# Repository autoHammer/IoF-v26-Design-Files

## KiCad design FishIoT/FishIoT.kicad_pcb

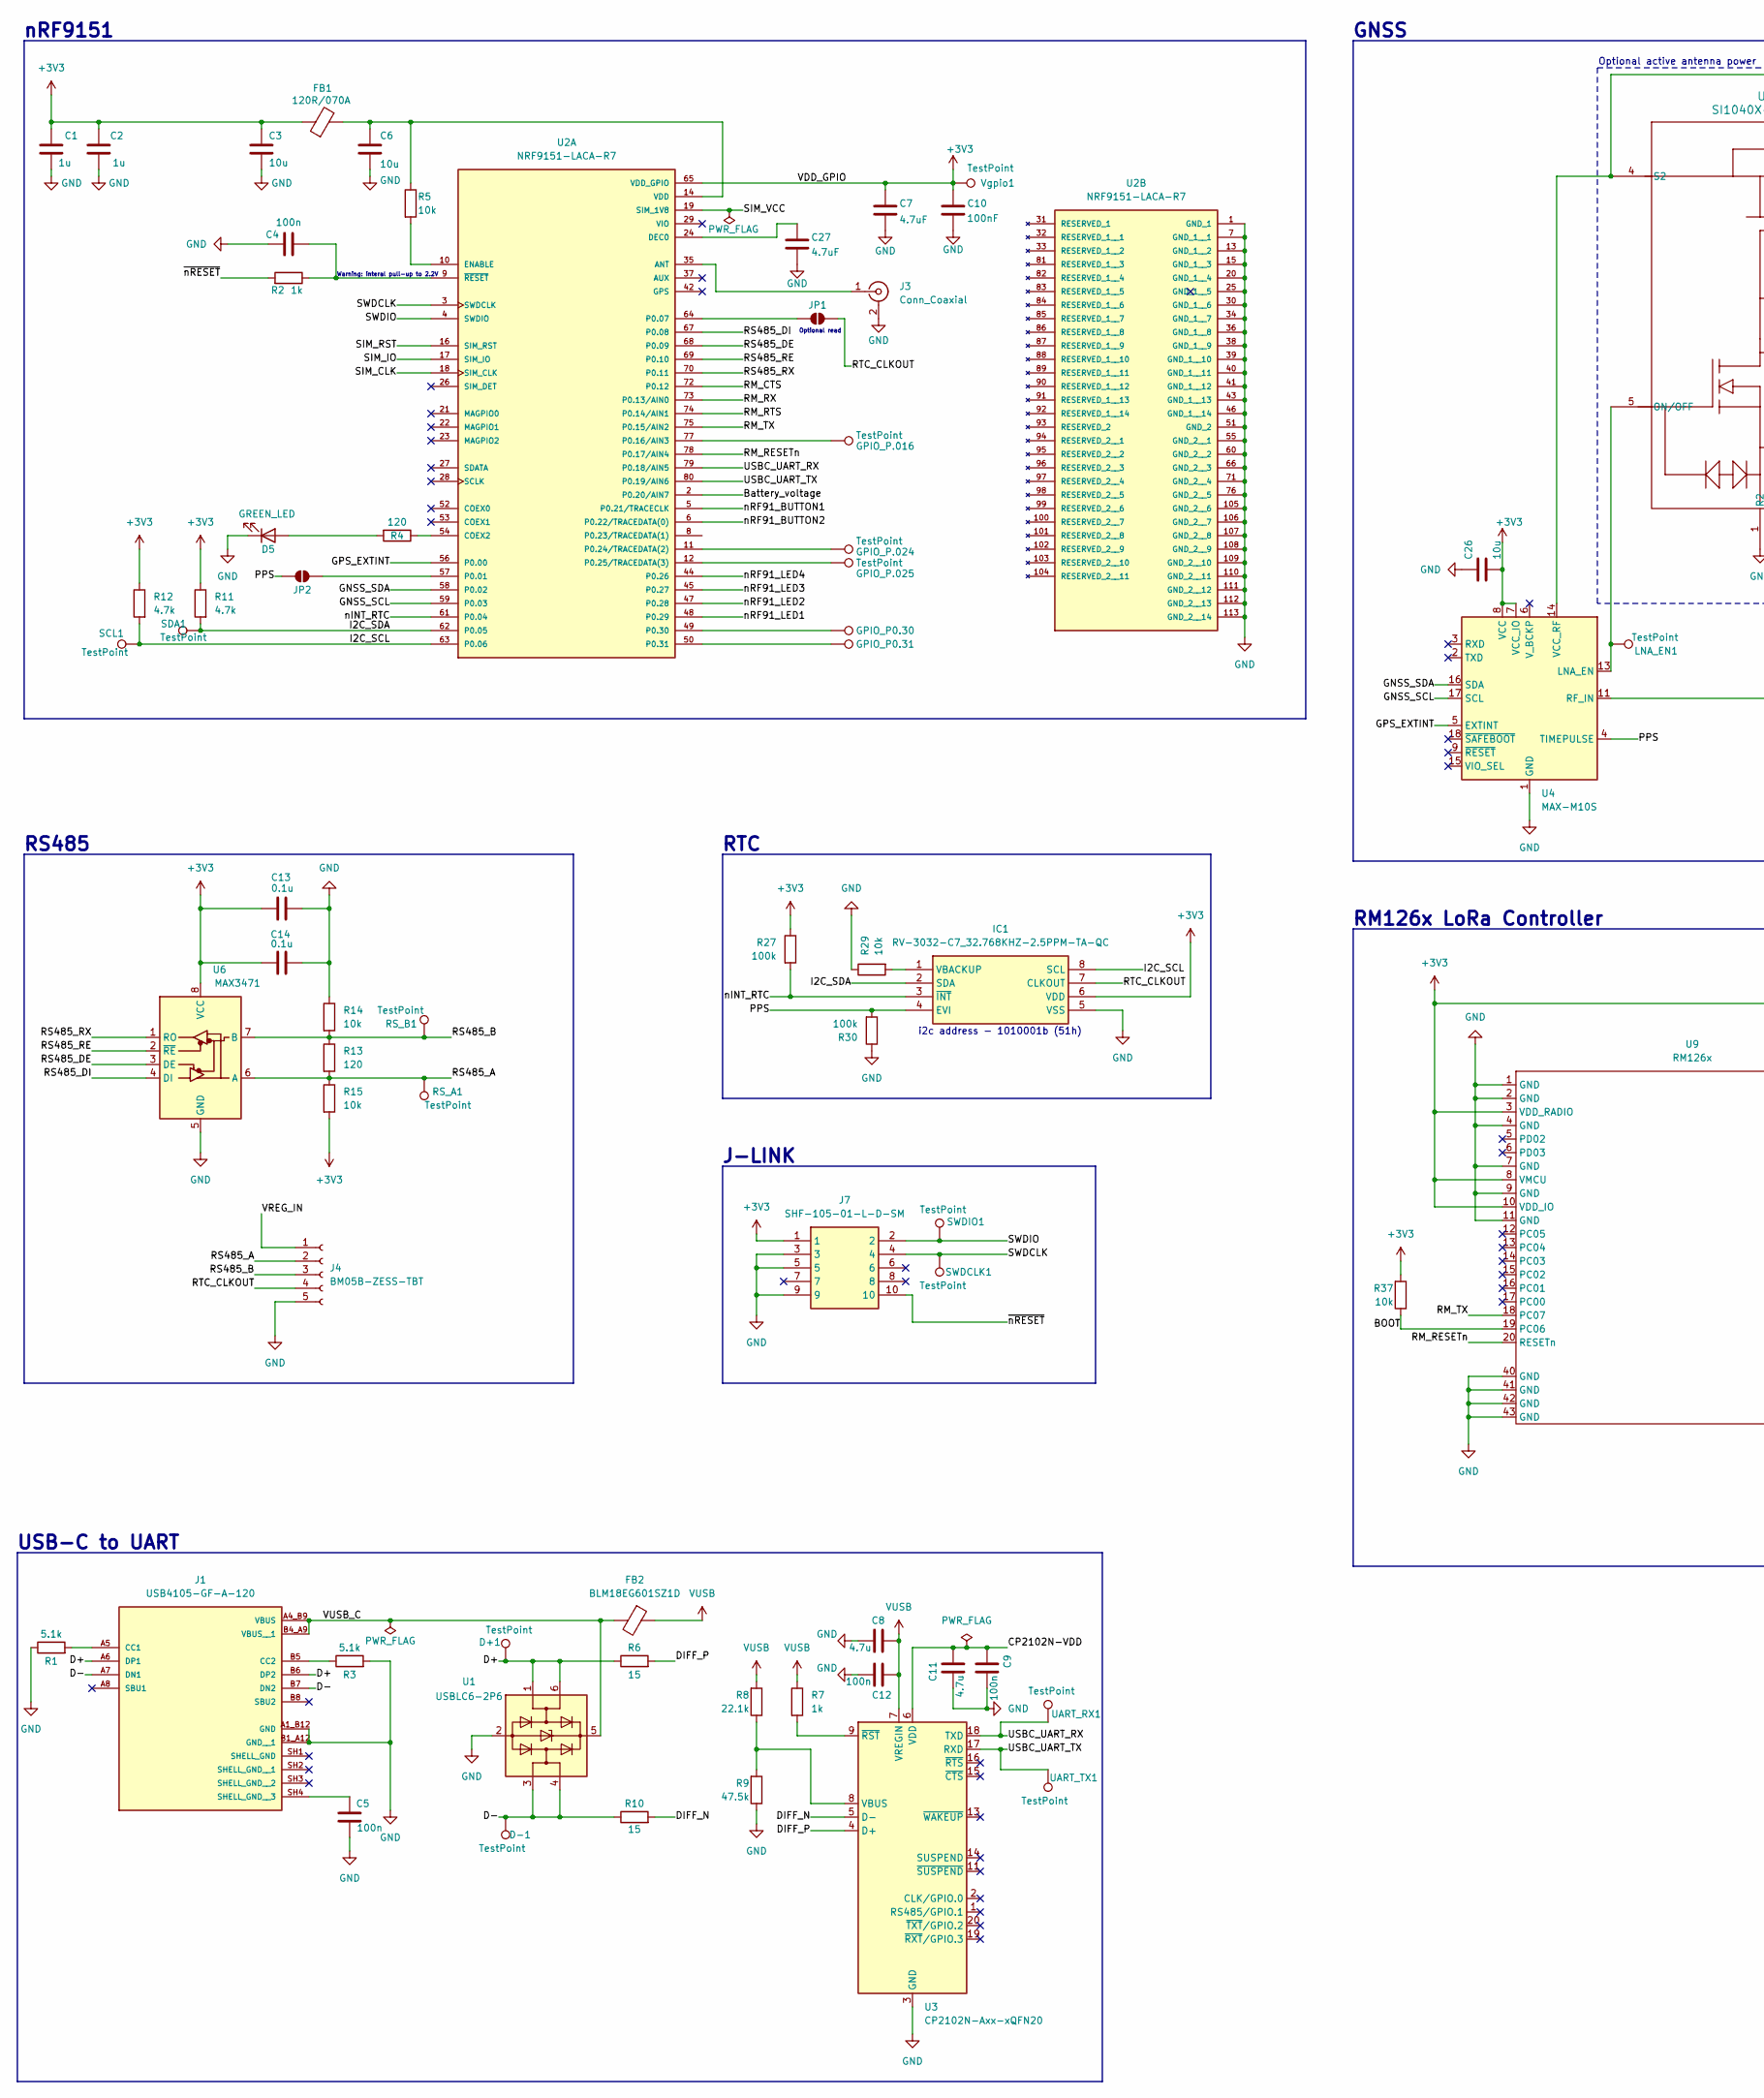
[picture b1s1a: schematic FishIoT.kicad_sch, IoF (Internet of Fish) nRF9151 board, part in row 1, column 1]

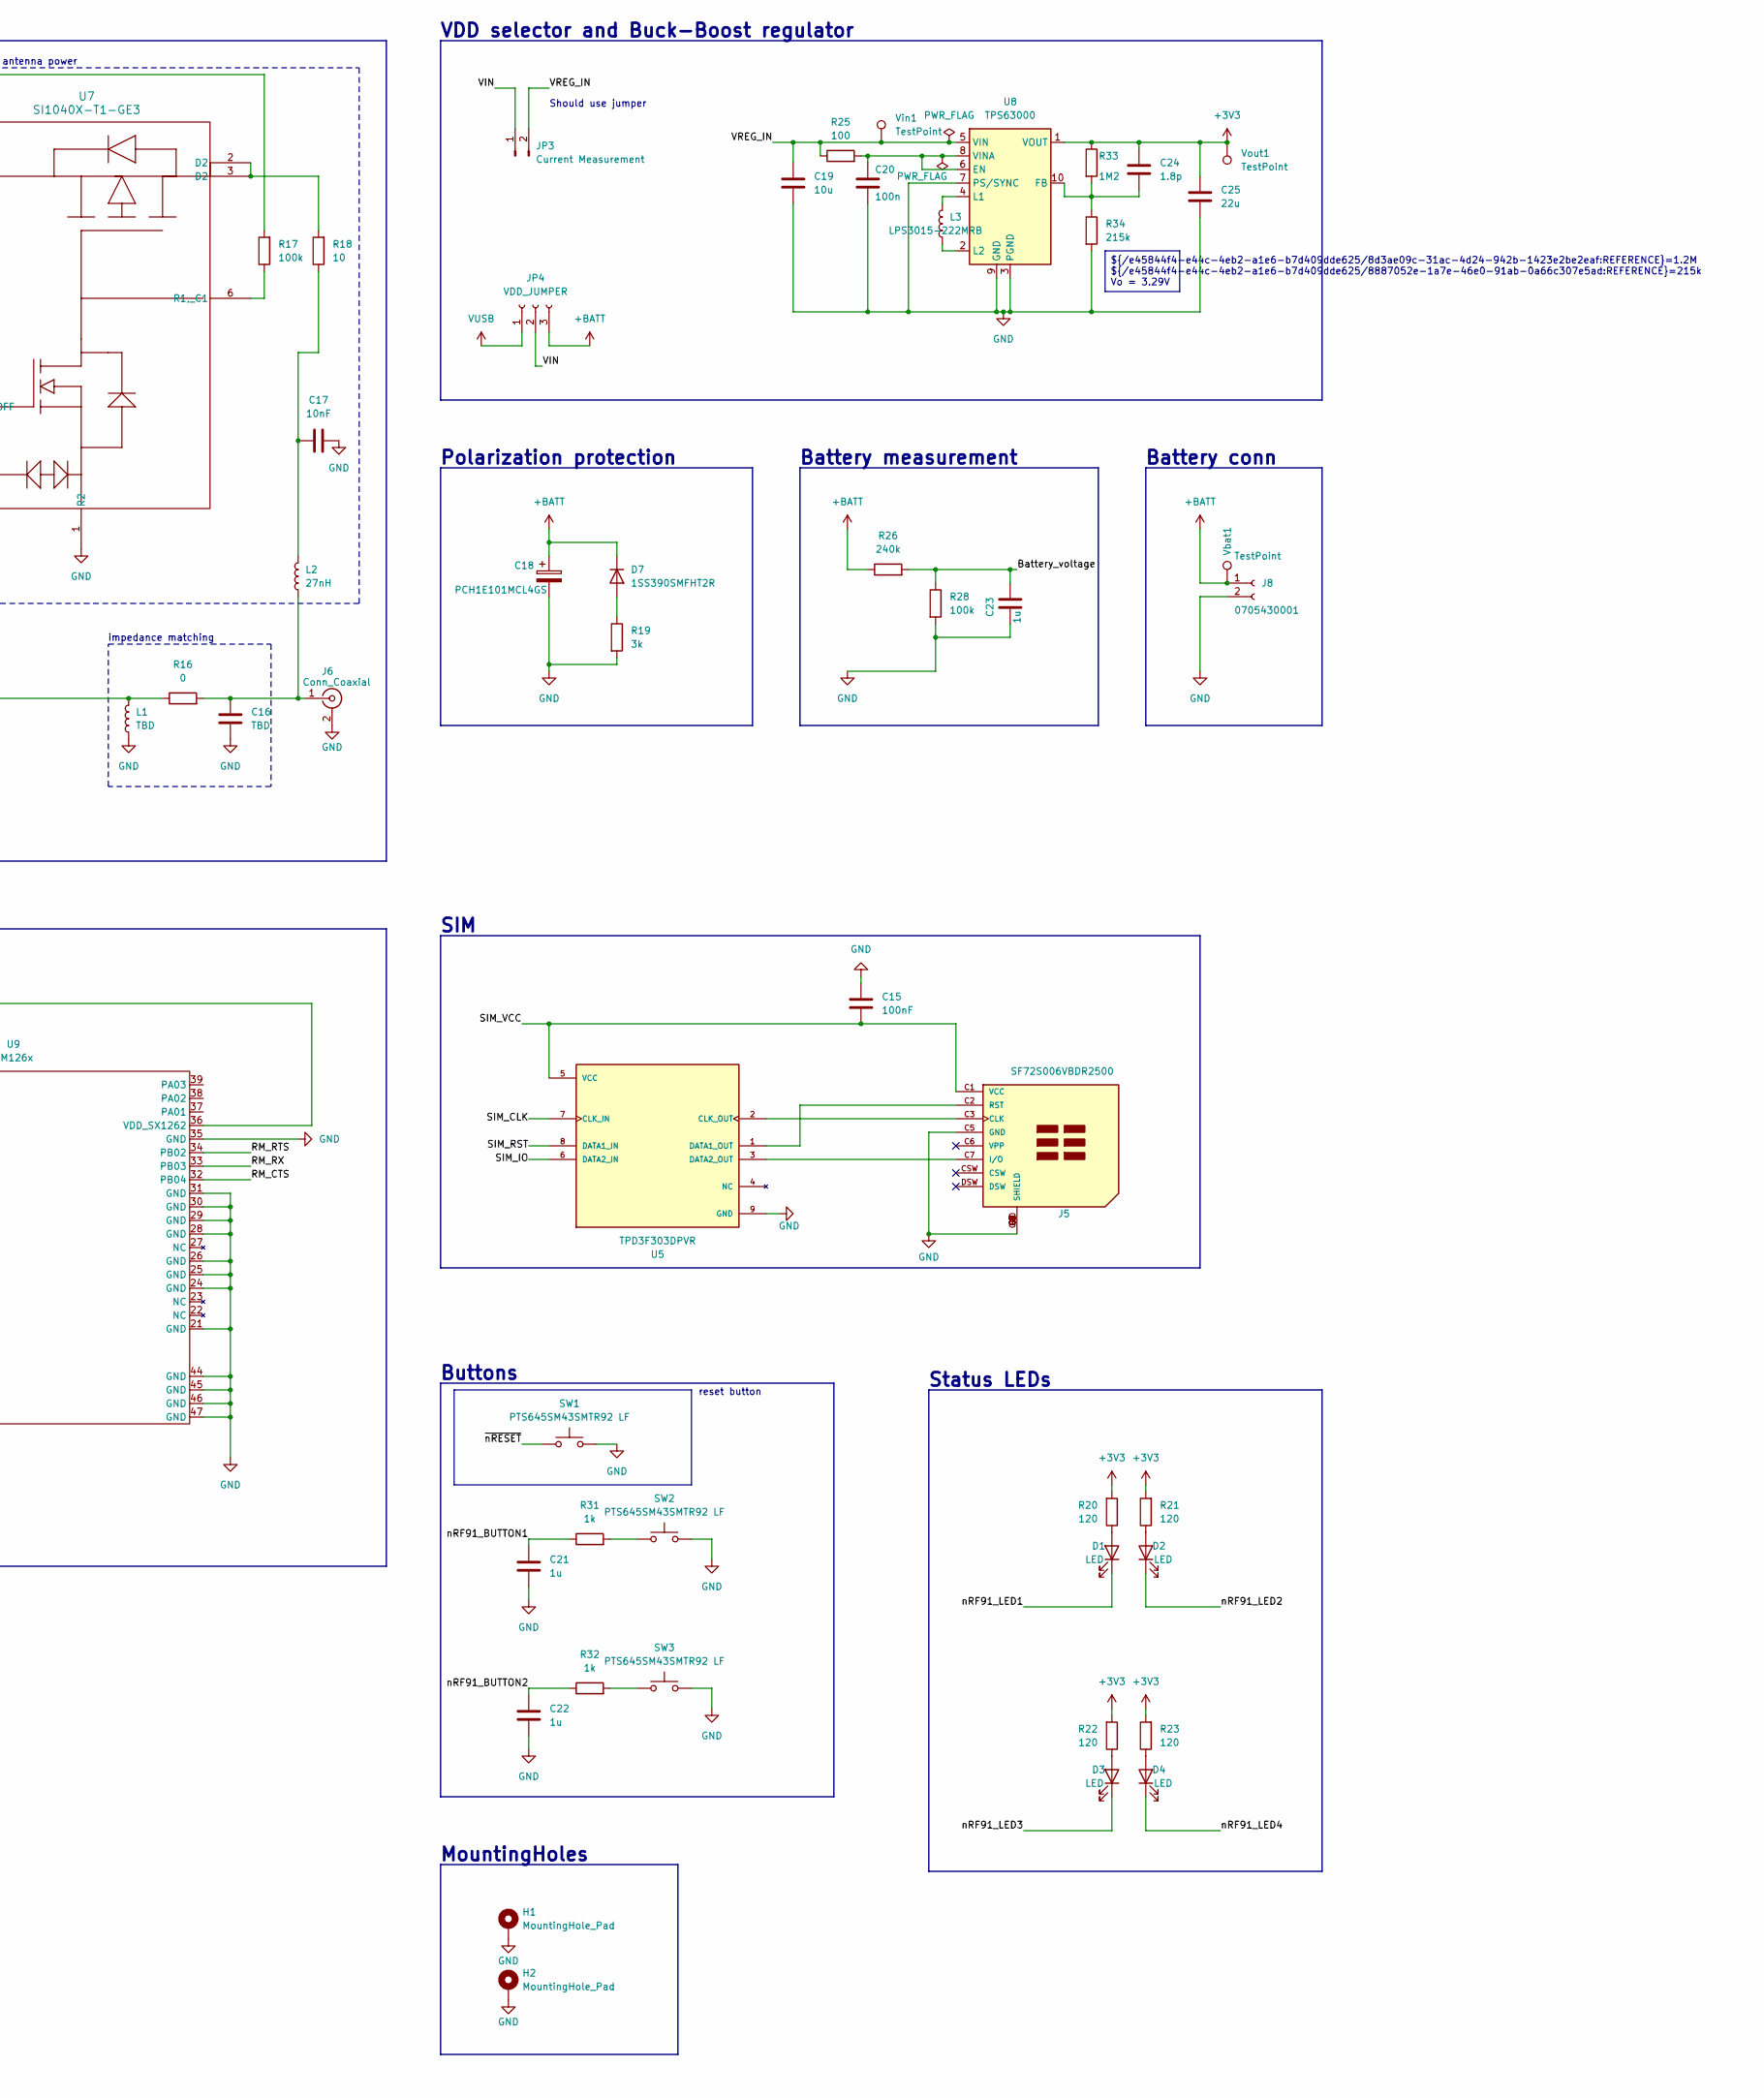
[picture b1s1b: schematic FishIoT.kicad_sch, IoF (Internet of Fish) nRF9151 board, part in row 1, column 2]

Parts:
C1, C2, C21, C22, C23: 1u; C_0603_1608Metric
C3, C6, C19, C26: 10u; C_0603_1608Metric
C4, C5, C9, C12, C20: 100n; C_0603_1608Metric
C7, C27: 4.7uF; C_0603_1608Metric
C8, C11: 4.7u; C_0603_1608Metric
C10, C15: 100nF; C_0603_1608Metric
C13, C14: 0.1u; C_0603_1608Metric
C16: TBD; C_0603_1608Metric
C17: 10nF; C_0603_1608Metric
C18: PCH1E101MCL4GS; CP_Elec_6.3x7.7
C24: 1.8p; C_0603_1608Metric
C25: 22u; C_0603_1608Metric
D1, D2, D3, D4: LED; LED_0603_1608Metric
D5: GREEN_LED; LED_0603_1608Metric
D7: 1SS390SMFHT2R; D_SOD-523
D+1: TestPoint; TestPoint_Pad_D1.0mm
D-1: TestPoint; TestPoint_Pad_D1.0mm
FB1: 120R/070A; L_0603_1608Metric
FB2: BLM18EG601SZ1D; L_0603_1608Metric
GPIO_P0.30, GPIO_P0.31, GPIO_P.016, GPIO_P.024, GPIO_P.025: TestPoint; TestPoint_Pad_D1.0mm
H1, H2: MountingHole_Pad; MountingHole_3mm_Pad_Via
IC1: RV-3032-C7_32.768KHZ-2.5PPM-TA-QC; RV3032C7; Mouser Part Number 428-203803-MG01
J1: USB4105-GF-A-120; GCT_USB4105-GF-A-120; PARTREV B3
J3, J6: Conn_Coaxial; LINX_CONUFL001-SMD-T
J4: BM05B-ZESS-TBT; BM05BZESSTBTLFSN
J5: SF72S006VBDR2500; JAE_SF72S006VBDR2500
J7: SHF-105-01-L-D-SM; SHF-105-01-X-D-SM; Mouser Part Number 200-SHF10501LDSM
J8: 0705430001; MOLEX_0705430001
JP1, JP2: SolderJumper_2_Open; SolderJumper-2_P1.3mm_Open_RoundedPad1.0x1.5mm
JP3: Current Measurement; PinHeader_1x02_P2.54mm_Vertical
JP4: VDD_JUMPER; PinHeader_1x03_P2.54mm_Vertical
L1: TBD; L_0603_1608Metric
L2: 27nH; L_0603_1608Metric
L3: LPS3015-222MRB; L_Vishay_IHLP-1212
LNA_EN1: TestPoint; TestPoint_Pad_D1.0mm
R1, R3: 5.1k; R_0603_1608Metric
R2, R7, R31, R32: 1k; R_0603_1608Metric
R4, R13, R20, R21, R22, R23: 120; R_0603_1608Metric
R5, R14, R15, R29, R37: 10k; R_0603_1608Metric
R6, R10: 15; R_0603_1608Metric
R8: 22.1k; R_0603_1608Metric
R9: 47.5k; R_0603_1608Metric
R11, R12: 4.7k; R_0603_1608Metric
R16: 0; R_0603_1608Metric
R17, R27, R28, R30: 100k; R_0603_1608Metric
R18: 10; R_0603_1608Metric
R19: 3k; R_0603_1608Metric
R25: 100; R_0603_1608Metric
R26: 240k; R_0603_1608Metric
R33: 1M2; R_0603_1608Metric
R34: 215k; R_0603_1608Metric
RS_A1: TestPoint; TestPoint_Pad_D1.0mm
RS_B1: TestPoint; TestPoint_Pad_D1.0mm
SCL1: TestPoint; TestPoint_Pad_D1.0mm
SDA1: TestPoint; TestPoint_Pad_D1.0mm
SW1, SW2, SW3: PTS645SM43SMTR92 LF; SW_Push_1P1T_NO_6x6mm_H9.5mm
SWDCLK1: TestPoint; TestPoint_Pad_D1.0mm
SWDIO1: TestPoint; TestPoint_Pad_D1.0mm
U1: USBLC6-2P6; SOT-666
U2: NRF9151-LACA-R7; XCVR_NRF9151-LACA-R7; PARTREV 2025-10-21
U3: CP2102N-Axx-xQFN20; SiliconLabs_QFN-20-1EP_3x3mm_P0.5mm_EP1.8x1.8mm
U4: MAX-M10S; ublox_MAX
U5: TPD3F303DPVR; SON50P210X160X65-9N
U6: MAX3471; TSSOP-8_3x3mm_P0.65mm
U7: SI1040X-T1-GE3; SON_0X-T1-GE3_VIS
U8: TPS63000; Texas_DRC0010J_ThermalVias
U9: RM126x; Laird, RM126X
UART_RX1: TestPoint; TestPoint_Pad_D1.0mm
UART_TX1: TestPoint; TestPoint_Pad_D1.0mm
Vbat1: TestPoint; TestPoint_Pad_D1.0mm
Vgpio1: TestPoint; TestPoint_Pad_D1.0mm
Vin1: TestPoint; TestPoint_Pad_D1.0mm
Vout1: TestPoint; TestPoint_Pad_D1.0mm

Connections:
+3V3: C1.2, C2.2, C3.2, C7.1, C10.1, C13.1, C14.2, C24.1, C25.1, C26.2, FB1.1, IC1.6 (VDD), J7.1, R11.1, R12.1, R15.2, R20.2, R21.2, R22.2, R23.2, R27.1, R33.1, R37.2, U2.65 (VDD_GPIO), U4.7 (VCC_IO), U4.8 (VCC), U6.8 (VCC), U8.1 (VOUT), U9.3 (VDD_RADIO), U9.8 (VMCU), U9.10 (VDD_IO), U9.36 (VDD_SX1262), Vgpio1.1, Vout1.1
+BATT: C18.1, D7.1 (K), J8.1, JP4.3, R26.1, Vbat1.1
/BOOT: R37.1, U9.19 (PC06)
/Battery_voltage: C23.2, R26.2, R28.1, U2.2 (P0.20/AIN7)
/CP2102N-VDD: C9.2, C11.2, U3.6 (VDD)
/D+: D+1.1, J1.A6 (DP1), J1.B6 (DP2), R6.1, U1.1 (I/O1), U1.6 (I/O1)
/D-: D-1.1, J1.A7 (DN1), J1.B7 (DN2), R10.1, U1.3 (I/O2), U1.4 (I/O2)
/DIFF_N: R10.2, U3.5 (D-)
/DIFF_P: R6.2, U3.4 (D+)
/GNSS_SCL: U2.59 (P0.03), U4.17 (SCL)
/GNSS_SDA: U2.58 (P0.02), U4.16 (SDA)
/GPS_EXTINT: U2.56 (P0.00), U4.5 (EXTINT)
/I2C_SCL: IC1.8 (SCL), R12.2, SCL1.1, U2.63 (P0.06)
/I2C_SDA: IC1.2 (SDA), R11.2, SDA1.1, U2.62 (P0.05)
/PPS: IC1.4 (EVI), JP2.2 (B), R30.2, U4.4 (TIMEPULSE)
/RM_CTS: U2.72 (P0.12), U9.32 (PB04)
/RM_RESETn: U2.78 (P0.17/AIN4), U9.20 (RESETn)
/RM_RTS: U2.74 (P0.14/AIN1), U9.34 (PB02)
/RM_RX: U2.73 (P0.13/AIN0), U9.33 (PB03)
/RM_TX: U2.75 (P0.15/AIN2), U9.18 (PC07)
/RS485_A: J4.2, R13.2, R15.1, RS_A1.1, U6.6 (A)
/RS485_B: J4.3, R13.1, R14.2, RS_B1.1, U6.7 (B)
/RS485_DE: U2.68 (P0.09), U6.3 (DE)
/RS485_DI: U2.67 (P0.08), U6.4 (DI)
/RS485_RE: U2.69 (P0.10), U6.2 (~RE)
/RS485_RX: U2.70 (P0.11), U6.1 (RO)
/RTC_CLKOUT: IC1.7 (CLKOUT), J4.4, JP1.2 (B)
/SIM_CLK: U2.18 (SIM_CLK), U5.7 (CLK_IN)
/SIM_IO: U2.17 (SIM_IO), U5.6 (DATA2_IN)
/SIM_RST: U2.16 (SIM_RST), U5.8 (DATA1_IN)
/SIM_VCC: C15.2, J5.C1 (VCC), U2.19 (SIM_1V8), U5.5 (VCC)
/SWDCLK: J7.4, SWDCLK1.1, U2.3 (SWDCLK)
/SWDIO: J7.2, SWDIO1.1, U2.4 (SWDIO)
/USBC_UART_RX: U2.79 (P0.18/AIN5), U3.18 (TXD), UART_RX1.1
/USBC_UART_TX: U2.80 (P0.19/AIN6), U3.17 (RXD), UART_TX1.1
/VIN: JP3.1, JP4.2
/VREG_IN: C19.1, J4.1, JP3.2, R25.1, U8.5 (VIN), Vin1.1
/VUSB_C: FB2.2, J1.A4_B9 (VBUS), J1.B4_A9 (VBUS__1), U1.5 (VBUS)
/nINT_RTC: IC1.3 (~INT), R27.2, U2.61 (P0.04)
/nRF91_BUTTON1: C21.1, R31.1, U2.5 (P0.21/TRACECLK)
/nRF91_BUTTON2: C22.1, R32.1, U2.6 (P0.22/TRACEDATA(0))
/nRF91_LED1: D1.1 (K), U2.48 (P0.29)
/nRF91_LED2: D2.1 (K), U2.47 (P0.28)
/nRF91_LED3: D3.1 (K), U2.45 (P0.27)
/nRF91_LED4: D4.1 (K), U2.44 (P0.26)
/~nRESET: J7.10, R2.2, SW1.1
GND: C1.1, C2.1, C3.1, C4.1, C5.1, C6.2, C7.2, C8.1, C9.1, C10.2, C11.1, C12.1, C13.2, C14.1, C15.1, C16.2, C17.2, C18.2, C19.2, C20.2, C21.2, C22.2, C23.1, C25.2, C26.1, C27.2, D5.1 (K), H1.1, H2.1, IC1.5 (VSS), J1.A1_B12 (GND), J1.B1_A12 (GND__1), J3.2 (Ext), J4.5, J5.C5 (GND), J5.G1 (SHIELD), J5.G2 (SHIELD), J5.G3 (SHIELD), J5.G4 (SHIELD), J5.G5 (SHIELD), J5.G6 (SHIELD), J5.G7 (SHIELD), J5.G8 (SHIELD), J5.G9 (SHIELD), J5.G10 (SHIELD), J6.2 (Ext), J7.3, J7.5, J7.9, J8.2, L1.1, R1.1, R3.2, R9.1, R14.1, R19.2, R28.2, R29.1, R30.1, R34.2, SW1.2, SW2.2, SW3.2, U1.2 (GND), U2.1 (GND_1), U2.7 (GND_1__1), U2.13 (GND_1__2), U2.15 (GND_1__3), U2.20 (GND_1__4), U2.25 (GND_1__5), U2.30 (GND_1__6), U2.34 (GND_1__7), U2.36 (GND_1__8), U2.38 (GND_1__9), U2.39 (GND_1__10), U2.40 (GND_1__11), U2.41 (GND_1__12), U2.43 (GND_1__13), U2.46 (GND_1__14), U2.51 (GND_2), U2.55 (GND_2__1), U2.60 (GND_2__2), U2.66 (GND_2__3), U2.71 (GND_2__4), U2.76 (GND_2__5), U2.105 (GND_2__6), U2.106 (GND_2__7), U2.107 (GND_2__8), U2.108 (GND_2__9), U2.109 (GND_2__10), U2.110 (GND_2__11), U2.111 (GND_2__12), U2.112 (GND_2__13), U2.113 (GND_2__14), U3.3 (GND), U3.12 (GND), U3.21 (GND), U4.1 (GND), U4.10 (GND), U4.12 (GND), U5.9 (GND), U6.5 (GND), U7.1 (R2), U8.3 (PGND), U8.7 (PS/SYNC), U8.9 (GND), U8.11 (PGND), U9.1 (GND), U9.2 (GND), U9.4 (GND), U9.7 (GND), U9.9 (GND), U9.11 (GND), U9.21 (GND), U9.24 (GND), U9.25 (GND), U9.26 (GND), U9.28 (GND), U9.29 (GND), U9.30 (GND), U9.31 (GND), U9.35 (GND), U9.40 (GND), U9.41 (GND), U9.42 (GND), U9.43 (GND), U9.44 (GND), U9.45 (GND), U9.46 (GND), U9.47 (GND)
unnamed: C17.1, L2.2, R18.1
unnamed: D1.2 (A), R20.1
unnamed: D2.2 (A), R21.1
unnamed: D3.2 (A), R22.1
unnamed: D4.2 (A), R23.1
unnamed: D5.2 (A), R4.2
unnamed: D7.2 (A), R19.1
unnamed: IC1.1 (VBACKUP), R29.2
unnamed: J1.A5 (CC1), R1.2
unnamed: J1.B5 (CC2), R3.1
unnamed: C5.2, J1.SH4 (SHELL_GND__3)
unnamed: J3.1 (In), U2.35 (ANT)
unnamed: J5.C3 (CLK), U5.2 (CLK_OUT)
unnamed: J5.C7 (I/O), U5.3 (DATA2_OUT)
unnamed: J5.C2 (RST), U5.1 (DATA1_OUT)
unnamed: C16.1, J6.1 (In), L2.1, R16.2
unnamed: JP1.1 (A), U2.64 (P0.07)
unnamed: JP2.1 (A), U2.57 (P0.01)
unnamed: R18.2, U7.2 (D2), U7.3 (D2)
unnamed: R31.2, SW2.1
unnamed: R32.2, SW3.1
unnamed: R4.1, U2.54 (COEX2)
unnamed: C27.1, U2.24 (DEC0)
unnamed: R5.2, U2.10 (ENABLE)
unnamed: GPIO_P.016.1, U2.77 (P0.16/AIN3)
unnamed: GPIO_P.024.1, U2.11 (P0.24/TRACEDATA(2))
unnamed: GPIO_P.025.1, U2.12 (P0.25/TRACEDATA(3))
unnamed: GPIO_P0.30.1, U2.49 (P0.30)
unnamed: GPIO_P0.31.1, U2.50 (P0.31)
unnamed: C6.1, FB1.2, R5.1, U2.14 (VDD)
unnamed: C4.2, R2.1, U2.9 (~RESET)
unnamed: R8.1, R9.2, U3.8 (VBUS)
unnamed: R7.2, U3.9 (~RST)
unnamed: LNA_EN1.1, U4.13 (LNA_EN), U7.5 (ON/OFF)
unnamed: L1.2, R16.1, U4.11 (RF_IN)
unnamed: R17.2, U4.14 (VCC_RF), U7.4 (S2)
unnamed: R17.1, U7.6 (R1,_C1)
unnamed: C20.1, R25.2, U8.6 (EN), U8.8 (VINA)
unnamed: C24.2, R33.2, R34.1, U8.10 (FB)
unnamed: L3.2, U8.4 (L1)
unnamed: L3.1, U8.2 (L2)
VUSB: C8.2, C12.2, FB2.1, JP4.1, R7.1, R8.2, U3.7 (VREGIN)

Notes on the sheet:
Optional read
MountingHoles
SIM
GNSS
Polarization protection
Optional active antenna power
Warning: interal pull-up to 2.2V
Battery conn
Status LEDs
RTC
nRF9151
i2c address - 1010001b (51h)
Buttons
RS485
VDD selector and Buck-Boost regulator
USB-C to UART
reset button
impedance matching
J-LINK
Should use jumper
RM126x LoRa Controller
Battery measurement
${/e45844f4-e44c-4eb2-a1e6-b7d409dde625/8d3ae09c-31ac-4d24-942b-1423e2be2eaf:REFERENCE}=1.2M ${/e45844f4-e44c-4eb2-a1e6-b7d409dde625/8887052e-1a7e-46e0-91ab-0a66c307e5ad:REFERENCE}=215k Vo = 3.29V

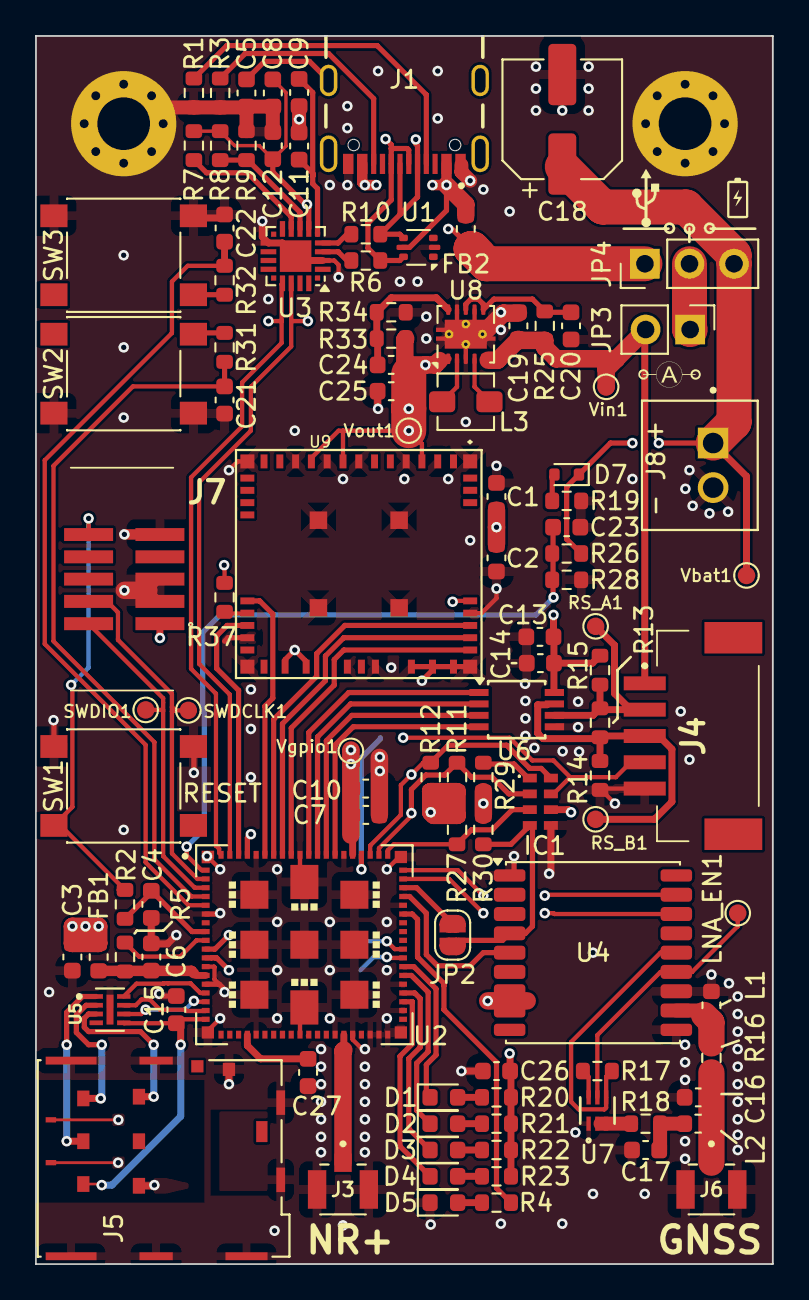
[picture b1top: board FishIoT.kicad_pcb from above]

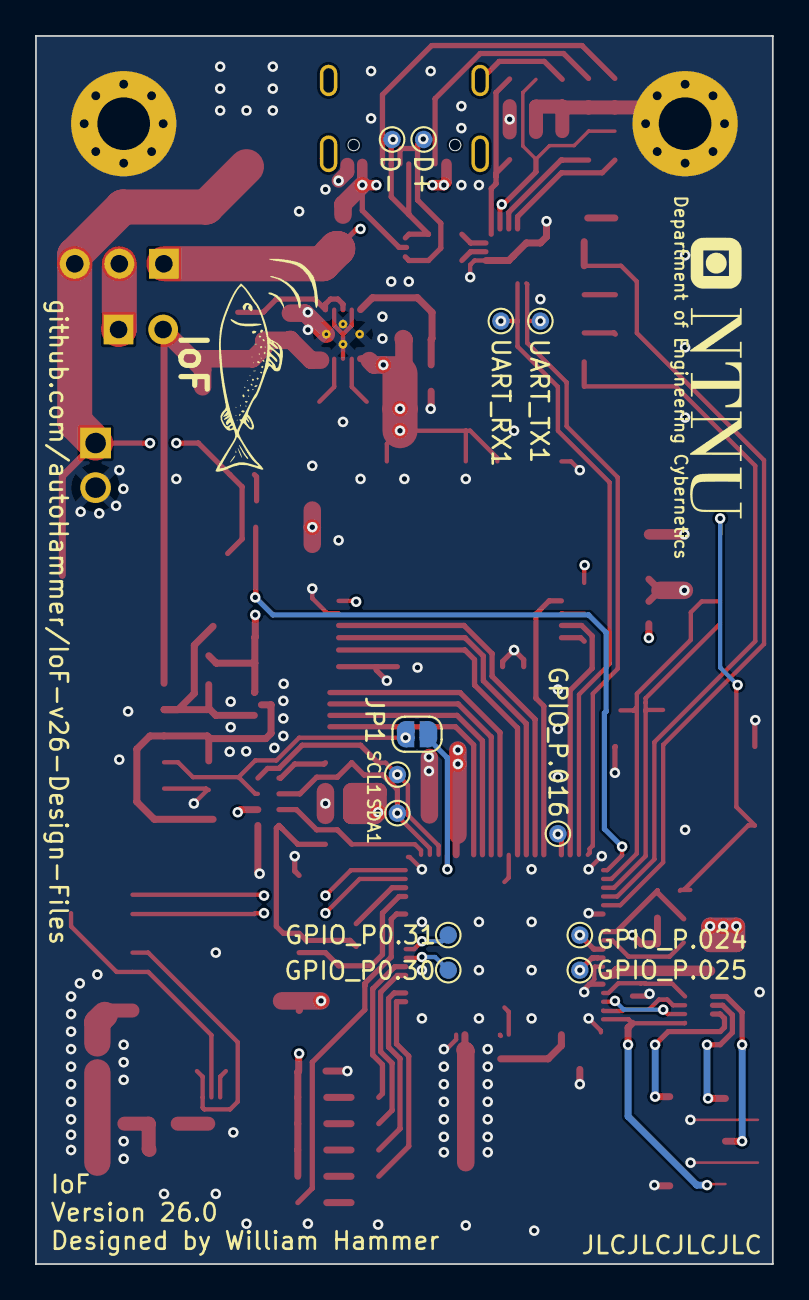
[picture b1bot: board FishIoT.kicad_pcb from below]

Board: 4 copper layers, 42.0 x 70.0 mm, 118 parts (12 on the bottom side), 89 nets.

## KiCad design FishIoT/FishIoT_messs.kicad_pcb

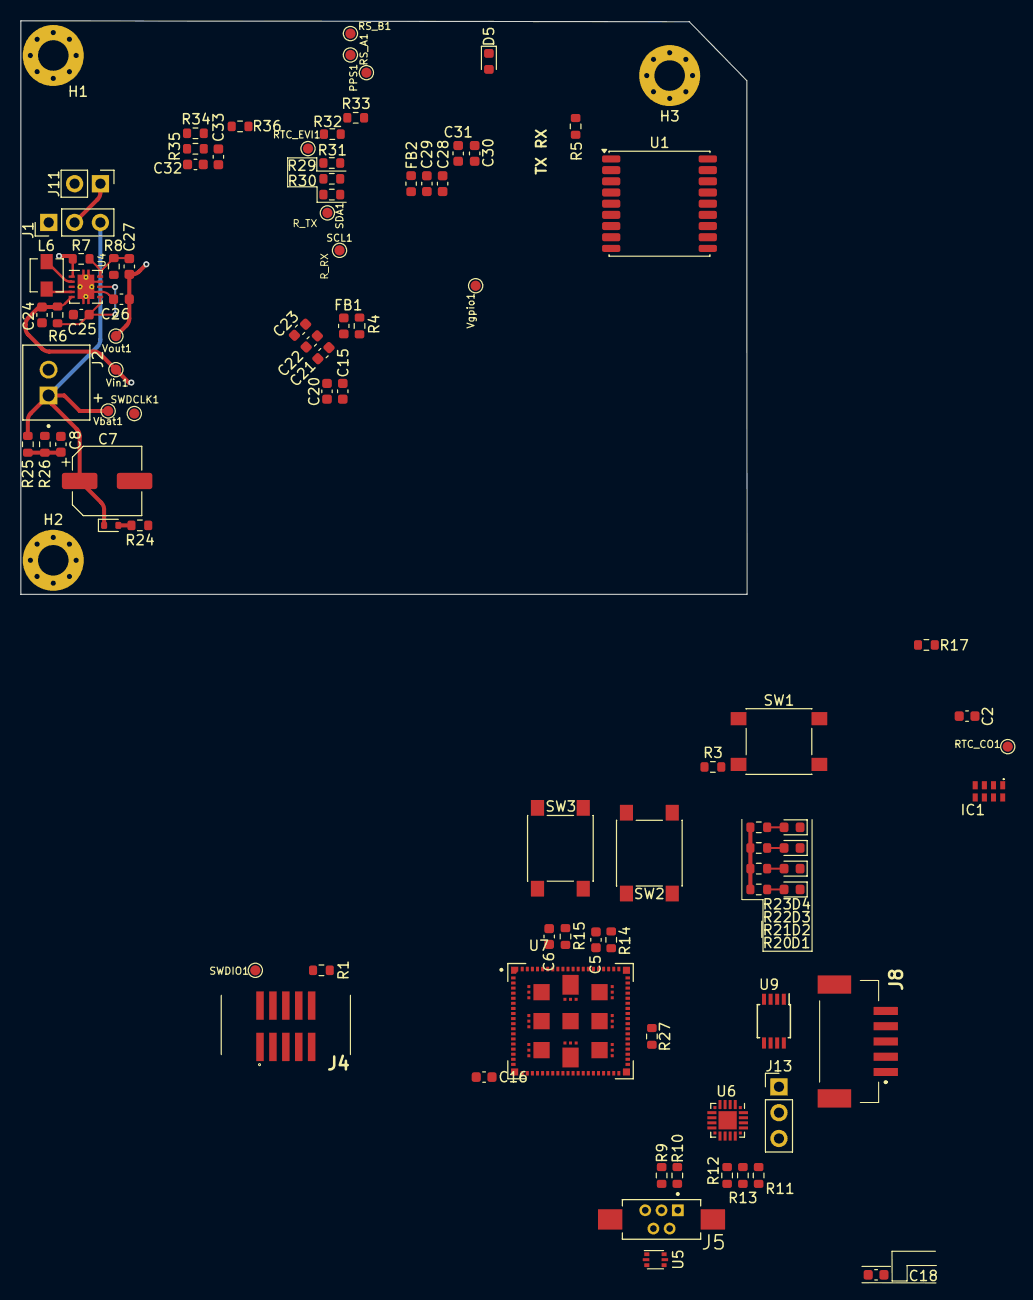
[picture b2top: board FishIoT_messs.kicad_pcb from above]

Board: 4 copper layers, 71.4 x 56.4 mm, 96 parts (1 on the bottom side), 59 nets.

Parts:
BT1: 3002; BAT_3002
C2, C16, C25, C28, C31: 100n; C_0603_1608Metric
C5, C6, C8, C22, C23: 1u; C_0603_1608Metric
C7: PCH1E101MCL4GS; CP_Elec_6.3x7.7
C15: 4.7uF; C_0603_1608Metric
C18, C21, C24: 10u; C_0603_1608Metric
C20: 100nF; C_0603_1608Metric
C26: 22u; C_0603_1608Metric
C27: 1.8p; C_0603_1608Metric
C29, C30: 4.7u; C_0603_1608Metric
C32, C33: 0.1u; C_0603_1608Metric
D1, D2, D3, D4: LED; LED_0603_1608Metric
D5: GREEN_LED; LED_0603_1608Metric
D6: 1SS390SMFHT2R; D_SOD-523
FB1: 120R/070A; L_0603_1608Metric
FB2: BLM18EG601SZ1D; L_0603_1608Metric
H1, H2, H3: MountingHole_Pad; MountingHole_3mm_Pad_Via
IC1: RV-3032-C7_32.768KHZ-2.5PPM-TA-QC; RV3032C7
J1: VDD_JUMPER; PinHeader_1x03_P2.54mm_Vertical
J2: 0705430001; MOLEX_0705430001
J4: SHF-105-01-L-D-SM; SHF-105-01-X-D-SM
J5: 10119313-302TLF; AMPHENOL_10119313-302TLF
J8: BM05B-ZESS-TBT; BM05BZESSTBTLFSN
J11: Current Measurement; PinHeader_1x02_P2.54mm_Vertical
J13: UART_DEBUG; PinHeader_1x03_P2.54mm_Vertical
L6: LPS3015-222MRB; L_Vishay_IHLP-1212
PPS1: TestPoint; TestPoint_Pad_D1.0mm
R1: 0R; R_0603_1608Metric
R3, R11, R14, R15: 1k; R_0603_1608Metric
R4, R34, R35: 10k; R_0603_1608Metric
R5, R17, R20, R21, R22, R23, R36: 120; R_0603_1608Metric
R6: 100; R_0603_1608Metric
R7: 1M2; R_0603_1608Metric
R8, R25: 240k; R_0603_1608Metric
R9, R10: 15; R_0603_1608Metric
R12: 22.1k; R_0603_1608Metric
R13: 47.5k; R_0603_1608Metric
R24: 3k; R_0603_1608Metric
R26, R31, R33: 100k; R_0603_1608Metric
R27, R32: 0; R_0603_1608Metric
R29, R30: 4.7k; R_0603_1608Metric
RS_A1: TestPoint; TestPoint_Pad_D1.0mm
RS_B1: TestPoint; TestPoint_Pad_D1.0mm
RTC_CO1: TestPoint; TestPoint_Pad_D1.0mm
RTC_EVI1: RTC_EVI; TestPoint_Pad_D1.0mm
SCL1: TestPoint; TestPoint_Pad_D1.0mm
SDA1: TestPoint; TestPoint_Pad_D1.0mm
SW1, SW2, SW3: PTS645SM43SMTR92 LF; SW_Push_1P1T_NO_6x6mm_H9.5mm
SWDCLK1: TestPoint; TestPoint_Pad_D1.0mm
SWDIO1: TestPoint; TestPoint_Pad_D1.0mm
U1: MAX-M10S; ublox_MAX
U4: TPS63000; Texas_DRC0010J_ThermalVias
U5: USBLC6-2P6; SOT-666
U6: CP2102N-Axx-xQFN20; SiliconLabs_QFN-20-1EP_3x3mm_P0.5mm_EP1.8x1.8mm
U7: NRF9151-LACA-R7; XCVR_NRF9151-LACA-R7
U9: MAX3471; TSSOP-8_3x3mm_P0.65mm
Vbat1: TestPoint; TestPoint_Pad_D1.0mm
Vgpio1: TestPoint; TestPoint_Pad_D1.0mm
Vin1: TestPoint; TestPoint_Pad_D1.0mm
Vout1: TestPoint; TestPoint_Pad_D1.0mm

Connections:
+3V3: C15.1, C20.1, C21.2, C22.2, C23.2, C26.1, C27.1, C32.2, C33.1, FB1.1, IC1.6 (VDD), J4.1, R7.1, R20.2, R21.2, R22.2, R23.2, R29.1, R30.1, R33.1, R34.2, U4.1 (VOUT), U7.65 (VDD_GPIO), U9.8 (VCC), Vgpio1.1, Vout1.1
+BATT: C7.1, D6.1 (K), J1.3, J2.1, R25.1, Vbat1.1
/Battery_voltage: C8.2, R25.2, R26.1, U7.73 (P0.13/AIN0)
/CP2102N-VDD: C30.2, C31.2, U6.6 (VDD)
/DIFF_N: R10.2, U6.5 (D-)
/DIFF_P: R9.2, U6.4 (D+)
/I2C_SCL: IC1.8 (SCL), R30.2, SCL1.1, U7.50 (P0.31)
/I2C_SDA: IC1.2 (SDA), R29.2, SDA1.1, U7.49 (P0.30)
/PPS: PPS1.1, R27.1, R32.2, U7.53 (COEX1)
/RS485_A: J8.2, R34.1, R36.1, RS_A1.1, U9.6 (A)
/RS485_B: J8.3, R35.2, R36.2, RS_B1.1, U9.7 (B)
/RS485_DE: U7.75 (P0.15/AIN2), U9.3 (DE)
/RS485_DI: U7.57 (P0.01), U9.4 (DI)
/RS485_RE: U7.74 (P0.14/AIN1), U9.2 (~RE)
/RS485_RX: U7.56 (P0.00), U9.1 (RO)
/RTC_CLOCKOUT: IC1.7 (CLKOUT), RTC_CO1.1, U7.44 (P0.26)
/SWDCLK: J4.4, SWDCLK1.1, U7.3 (SWDCLK)
/SWDIO: J4.2, SWDIO1.1, U7.4 (SWDIO)
/TBR_PPS: J8.4, U7.77 (P0.16/AIN3)
/VIN: J1.2, J11.1
/VREG_IN: C24.1, J8.1, J11.2, R6.1, U4.5 (VIN), Vin1.1
/nINT_RTC: IC1.3 (~INT), R33.2, U7.72 (P0.12)
/nRF91_BUTTON1: C5.1, R14.1, U7.63 (P0.06)
/nRF91_BUTTON2: C6.1, R15.1, U7.68 (P0.09)
/nRF91_LED1: D1.1 (K), U7.58 (P0.02)
/nRF91_LED2: D2.1 (K), U7.59 (P0.03)
/nRF91_LED3: D3.1 (K), U7.61 (P0.04)
/nRF91_LED4: D4.1 (K), U7.62 (P0.05)
/nRF_UART_RX: J13.2, U6.18 (TXD), U7.47 (P0.28)
/nRF_UART_TX: J13.3, U6.17 (RXD), U7.48 (P0.29)
/~nRESET: R1.2, R3.1, SW1.1
GND: BT1.N, C2.1, C5.2, C6.2, C7.2, C8.1, C15.2, C16.1, C18.2, C20.2, C21.1, C22.1, C23.1, C24.2, C25.2, C26.2, C28.1, C29.1, C30.1, C31.1, C32.1, C33.2, D5.1 (K), H1.1, H2.1, H3.1, IC1.5 (VSS), J2.2, J4.3, J4.5, J4.9, J5.4 (GND), J5.5 (Shield), J8.5, J13.1, R8.2, R13.1, R24.2, R26.2, R31.1, R35.1, SW1.2, SW2.2, SW3.2, U1.1 (GND), U1.10 (GND), U1.12 (GND), U4.3 (PGND), U4.7 (PS/SYNC), U4.9 (GND), U4.11 (PGND), U5.2 (GND), U6.3 (GND), U6.12 (GND), U6.21 (GND), U7.1 (GND_1), U7.7 (GND_1__1), U7.13 (GND_1__2), U7.15 (GND_1__3), U7.20 (GND_1__4), U7.25 (GND_1__5), U7.30 (GND_1__6), U7.34 (GND_1__7), U7.36 (GND_1__8), U7.38 (GND_1__9), U7.39 (GND_1__10), U7.40 (GND_1__11), U7.41 (GND_1__12), U7.43 (GND_1__13), U7.46 (GND_1__14), U7.51 (GND_2), U7.55 (GND_2__1), U7.60 (GND_2__2), U7.66 (GND_2__3), U7.71 (GND_2__4), U7.76 (GND_2__5), U7.105 (GND_2__6), U7.106 (GND_2__7), U7.107 (GND_2__8), U7.108 (GND_2__9), U7.109 (GND_2__10), U7.110 (GND_2__11), U7.111 (GND_2__12), U7.112 (GND_2__13), U7.113 (GND_2__14), U9.5 (GND)
unnamed: BT1.P1, R17.1
unnamed: D1.2 (A), R20.1
unnamed: D2.2 (A), R21.1
unnamed: D3.2 (A), R22.1
unnamed: D4.2 (A), R23.1
unnamed: D5.2 (A), R5.2
unnamed: D6.2 (A), R24.1
unnamed: IC1.4 (EVI), R31.2, R32.1, RTC_EVI1.1
unnamed: C2.2, IC1.1 (VBACKUP), R17.2
unnamed: J4.10, R1.1
unnamed: J5.3 (D+), R9.1, U5.1 (I/O1), U5.6 (I/O1)
unnamed: J5.2 (D-), R10.1, U5.3 (I/O2), U5.4 (I/O2)
unnamed: FB2.2, J5.1 (VBUS), U5.5 (VBUS)
unnamed: R14.2, SW2.1
unnamed: R15.2, SW3.1
unnamed: C25.1, R6.2, U4.6 (EN), U4.8 (VINA)
unnamed: C27.2, R7.2, R8.1, U4.10 (FB)
unnamed: L6.2, U4.4 (L1)
unnamed: L6.1, U4.2 (L2)
unnamed: R12.1, R13.2, U6.8 (VBUS)
unnamed: R11.2, U6.9 (~RST)
unnamed: R5.1, U7.54 (COEX2)
unnamed: R4.2, U7.10 (ENABLE)
unnamed: R27.2, U7.45 (P0.27)
unnamed: C18.1, FB1.2, R4.1, U7.14 (VDD)
unnamed: C16.2, R3.2, U7.9 (~RESET)
VBUS: C28.2, C29.2, FB2.1, J1.1, R11.1, R12.2, U6.7 (VREGIN)

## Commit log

2026-02-12 v26.0
    First draft of schematics and PCB with nRF9151
2026-02-16 Added LoRa module
2026-02-20 Ordered v26.0
2026-05-23 Schematics cleanup
2026-05-24 fixed battery measurement, DEC0 capacitor and I2C for GNSS
2026-06-17 Updated README.md with schematics of v26.0
